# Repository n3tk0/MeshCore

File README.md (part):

> **This is a fork of [meshcore-dev/MeshCore](https://github.com/meshcore-dev/MeshCore).**
> It tracks upstream and adds a Faketec v5 companion build with its own encoder-driven UI (read and write messages without a phone), a mailbox and LoRa OTA updates for repeaters (with an Android app and an nRF52 bootloader that survives power cuts), light builds of any board, plus robustness fixes to the shared MeshCore code.
> Everything below "About MeshCore" is the upstream README. For general MeshCore support, issues and contributions, please use the upstream repository.

## 🍴 What this fork adds

- [Faketec v5 companion with encoder UI](#faketec-v5-companion-with-encoder-ui): hardware, wiring, controls, writing messages, settings, build flags
- [Repeater mailbox](#repeater-mailbox-store--forward-for-direct-messages): keeps direct messages for owners who are away
- [LoRa OTA for repeaters](#lora-ota-for-repeaters-nrf52-esp32): delta updates over the air from an Android app
- [Repeater battery from an INA219](#repeater-battery-from-an-ina219) and [repeaters that look after themselves](#repeaters-that-look-after-themselves): charge counting, battery saving steps (`battsave`), self test, telemetry history
- [nRF52 bootloader for LoRa OTA](#nrf52-bootloader-for-lora-ota): staged install that survives a power cut, rollback on boards with QSPI flash
- [Fixes to upstream MeshCore](#fixes-to-upstream-meshcore): crash and hang fixes that apply to every board
- [New shared components](#new-shared-components): reusable drivers and hooks added under `src/` and `examples/companion_radio/`
- [Builds and CI](#builds-and-ci)

> Status: the Faketec v5 firmware compiles and boots with BLE. The UI has been checked in the screen simulator (`tools/ui-sim`); the latest changes (network tools, channels from the device, learned words, hardware check, buttons instead of the encoder, repeat) have not been tested on hardware yet. The repeater mailbox, LoRa OTA and the bootloader pass their unit and host tests and build in CI, but have not been tested on hardware yet either; neither have the battery steps, self test, telemetry history and the app's Health and "Update several" pages.

### Faketec v5 companion with encoder UI

A companion radio build for a Faketec v5 (rev A) board without the on-board BMS/MOSFET, with a local screen and jog-dial controls so the node can be used without a phone. User manual in Bulgarian: [docs/faketec-companion.bg.md](./docs/faketec-companion.bg.md).

| Part | Used here |
|---|---|
| MCU | Nice!Nano v2 / nRF52840 Pro Micro clone |
| Radio | Heltec HT-RA62 (SX1262) |
| Display | 128x64 SSD1306 I2C OLED (e.g. WINSTAR WEA012864) |
| Encoder | Quadrature rotary encoder with push switch (e.g. ZIPPY AN-P1S-2SP-Z), or three buttons instead (see below) |
| Buttons | User button (Back) and reset; use 2-pin switches, a 4-pin switch shorts on the SW1/SW2 footprint |
| Haptics | 3 V coin vibration motor on the board's T2 MOSFET footprint (optional) |
| Power | 1S LiPo straight from the controller's charger, battery read through a divider |

**Wiring**

| Function | Pin |
|---|---|
| Encoder A / B | P1.01 / P1.02 (common to GND) |
| Encoder push | P1.07 |
| Buttons instead of the encoder | Up P1.01, Down P1.02, Enter P1.07 (each to GND) |
| User button (Back) | P1.00 |
| OLED SDA / SCL | P1.04 / P0.11 (board I2C) |
| Vibration motor | T2 gate = P0.08, motor between B+ and drain pad J7, flyback diode across the motor |

**Controls** (Sony Ericsson CMD-Z7 style jog dial, UI in [`examples/companion_radio/ui-encoder`](./examples/companion_radio/ui-encoder))

| Input | Action |
|---|---|
| Turn | Move in lists, scroll a conversation; on standby, next status card (summary, recently heard, radio, battery, GPS) |
| Press | Open / confirm; in a conversation, reply to the selected message |
| Hold press | Quick menu (advert nearby, advert to the whole mesh, transmit on/off, Bluetooth, GPS, power off) or the actions of the current item |
| Back (BTN) | Back one level; on standby, screen off |
| Hold Back | Standby from anywhere; on standby, lock the keys (hold Back again to unlock); while the boot splash shows, CLI rescue |
| Hold Back + press 2.5 s | Power off ("Power off" shows, a double buzz confirms; does nothing while the keys are locked). To switch on, hold Back + press together ~1.5 s until it buzzes; a shorter press goes back to sleep. With USB power it starts at once. In quiet mode neither buzzes |

**Messages**

- **Messages** lists conversations (contacts and channels), newest first, with the unread count or the age of the last message. A conversation opens as a chat: every message wrapped over as many rows as it needs, my messages with their delivery icon, the age of the selected one in the title. Press replies, hold opens Reply / Resend / Delete.
- **Channels** opens a channel's conversation (or the reply picker when it has none yet). Hold on a channel: write, mute (no buzz or screen wake, except for mentions; stored in `/ui_mute`) or delete. The last row, **+ Add**, joins a `#hashtag` channel typed on the keyboard (key = first 16 bytes of `sha256("#name")`, the same as the app).
- **Message details:** hold on a message > Details shows the time, the route (direct / flood / hops), SNR and RSSI of a received message, or the attempts and state of a sent one.
- **Reply** first asks **Quick reply** or **Write**. A quick reply can be sent as is or finished on the keyboard. Replies go to where the message came from (contact or channel).
- **Sending** waits 3 s with a progress bar; Back cancels it. Direct messages are tracked: a clock until the ACK, then a check mark. Without an ACK the message is sent again automatically with the same timestamp (the recipient shows it once), the last attempt as a flood; after 3 attempts it is marked not delivered with a long vibration, and **Resend** starts a new round. Channel messages have no ACK and show as sent.
- **Mentions:** a channel message with `@name` or `@[name]` for this node vibrates and wakes the screen like a direct message.
- **Recipient list:** channels (`#`) first, then chat and room contacts, sorted by name or by last heard. Sorted by name, a row of first letters sits on top: turn left from the first entry, press, turn to a letter, press to jump to the first name with it.
- **Keyboard:** BG, EN and 123 layouts with shift (automatic capital at the start and after `. ! ?`), space, language and send keys. Turn to pick a key, press to type, Back deletes, hold opens Send / Clear / Discard. An unsent message is kept for its recipient while you write elsewhere.
- **Next word:** after a space, the word you most often sent after the previous one is suggested (pairs learned from sent messages, up to 192, ~3.5 KB in `/ui_pairs`; punctuation breaks the chain; Settings > Messages > Learned words > Clear also clears them).
- **Word prediction:** the most frequent dictionary word for what you are typing is shown after the cursor and is selected right after each letter: **press** accepts it and adds a space, turning goes back to the keys. The dictionary (6000 Bulgarian + 4000 English words, ~71 KB flash) is chosen by the script you type in; words you typed recently are suggested first. It is generated by [`ui-encoder/tools/gen_dict.py`](./examples/companion_radio/ui-encoder/tools/gen_dict.py) from [FrequencyWords](https://github.com/hermitdave/FrequencyWords) (CC-BY-SA-4.0). Learned words: words you send that the dictionary lacks (names, places, slang; 3+ letters) are learned, up to 128, stored in `/ui_words`, and suggested before dictionary words.
- **Nothing is lost before the app syncs:** every message for the phone app is written to flash as it arrives (`-D OFFLINE_QUEUE_PERSIST`, an append-only log) and leaves it only when the app has fetched it, so it survives a reset, a hang or a flat battery (up to 256 messages; when full, the oldest channel messages go first). The device's own history (last 24) is not cleared by a sync; it is written within 10 minutes of a change, at power off and before an update. Messages sent from the device do not appear in the phone app's history.

- **Quiet hours:** Settings > Messages > Quiet hours (off, 22–07, 23–07, 00–07, 22–06, 23–06): in those hours channel messages neither wake the screen nor vibrate; direct messages and mentions still do. Only with a valid clock (from the app or an advert); without one it is off.
- **"I'm back":** after a power-on or a wake from sleep/hibernate, and when a repeater is heard again after 10+ minutes without one (its advert, or any flood packet it passes on, so a node that stays near a repeater does not do it every hour), the companion sends one zero-hop advert by itself (at most once in 10 minutes, only while transmit is on), so a repeater's mailbox hands over at once (`-D BACK_ADVERT`). When the mailbox delivers, the screen shows "Mailbox: N msgs".
- **Battery:** the battery card shows the voltage and the time left (e.g. `3.8V ~18h`), from how fast the percentage fell over the last hours; the next card is a 24-hour graph of the battery with its low–high %. The history (every 10 minutes for 24 h, every hour for a week, `-D TELEMETRY_HISTORY`) is kept in `/tele_hist` and the app reads it (BLE command 121).

**Network** (Menu > Network)

- **Nearby:** a zero-hop discover request; the repeaters that answer in 10 s, strongest first. A repeater shows how well it hears us (↑) and we hear it (↓), and starts a trace or range test to it. Hold searches again.
- **Trace:** from a contact (hold > Trace) or a nearby repeater: a TRACE packet there and back through the repeaters of its path, with the SNR at each hop and the round-trip time.
- **Airtime:** transmit time in the last hour against the EU 868 MHz 10% duty cycle, total TX time, packets sent / received / errors, noise floor, last SNR and RSSI.
- **Range test:** a trace to the chosen repeater or contact every 15 / 30 / 60 / 120 s, a buzz for each answer (a different one for a miss), the last results with SNR there and back. Keeps running with the screen off until stopped (an icon in the standby status row shows it); stops if transmit is switched off.

**Settings** (Menu > Settings, saved in prefs)

| Group | Settings |
|---|---|
| Display | menu font and text font size (large / medium / small / tiny), screen timeout (15 s – 5 min), brightness, page dots |
| Hardware | encoder direction, encoder steps per detent (2 / 4; hidden with buttons), vibration, keyboard jump to the likely next letter, key lock (by hand / automatic when the screen goes off), input test, vibration test, screen test, readings (battery raw/ADC, USB, reset reason, noise floor, uptime) |
| Messages | alerts (without phone / always / never), wake the screen for (direct and mentions / all / never), quiet hours, confirm deletes, contacts sort, 10 quick replies (stored in `/ui_quick`), learned words (count, clear) |
| Radio | transmit on/off, TX power, antenna question (after a new battery / every boot / never), preset (EU/UK Narrow, EU/UK Deprecated; anything else shows as custom), repeater |
| System | node name (an advert with the new name is offered; the Bluetooth name changes after a restart), language BG / EN, time zone, EU summer time, battery calibration, about, CLI rescue, firmware update over USB (UF2 drive) or BLE (DFU) |

**Buttons instead of the encoder:** Up on P1.01, Down on P1.02 and Enter on P1.07, each to GND. The firmware is the same: after a new battery, the first turn or press at the antenna question shows which is fitted, and that is remembered across restarts and power off. A held button repeats. A wrong guess fixes itself: two full encoder clicks in one direction within 1 s switch to the encoder, two presses of one button within 2 s switch to buttons.

**Repeater (emergency only):** Settings > Radio > Repeater (or the phone app) makes the companion repeat other nodes' packets. It loads the mesh and the battery, so it asks "Emergency only! Turn on?" first, and a tower icon shows in the status row while it is on. It is allowed on 433.000, 869.495, 869.618 (EU/UK Narrow) and 918.000 MHz (`-D ALLOWED_REPEAT_FREQ_RANGE` in the Faketec ini); while it is on, a preset on another frequency is refused.

**Battery calibration:** Settings > System > Battery shows the measured voltage; set it to what a multimeter shows at the battery and the divider factor is saved in prefs. The shown value is averaged, and the node powers off only after three low readings in a row, so a transmit pulse does not switch it off.

**Watchdog:** the nRF52 hardware watchdog (30 s, `-D WATCHDOG_SECONDS`) restarts a node whose main loop hangs, e.g. on a stuck I2C bus, so the low-battery cutoff keeps working. The bootloader feeds it, so DFU and UF2 updates are not affected.

**Build flags** (in [`variants/faketec_v5/platformio.ini`](./variants/faketec_v5/platformio.ini))

- `-D DISPLAY_CYRILLIC`: Cyrillic 5x8 font for the SSD1306.
- `-D PIN_VIBRATION`, `-D VIBRATION_PWM=190`: haptic patterns (key click, confirm, channel / direct message, power off); PWM keeps the motor near 3.1 V on a full LiPo. Remove to build without a motor.
- `-D AUTO_SHUTDOWN_MILLIVOLTS=3300`: there is no BMS, so the node hibernates below this voltage. Calibrate in Settings > System > Battery (or set `-D ADC_MULTIPLIER` for your divider).
- `-D ENCODER_STEPS_PER_DETENT=2`, `-D ENCODER_REVERSE=true`: build defaults for the encoder; both can also be changed in Settings.
- `-D DISABLE_RTC_AUTODISCOVERY`, `-D DISABLE_ENV_SENSORS`: skip the RTC probes and the sensor scan when none are fitted (a faster boot; a bad I2C bus no longer hangs it, see below).
- `-D ALLOWED_REPEAT_FREQ_RANGE=...`: the frequencies where the repeater setting may be turned on (upstream allows 433.000, 869.495 and 918.000 MHz; this build adds 869.618).

Build with PlatformIO, e.g. `pio run -e Faketec_v5_companion_radio_ble` (or `_usb`), then flash the UF2 by double-tapping reset and copying it to the bootloader drive.

### Repeater mailbox (store & forward for direct messages)

Every repeater built from this fork (`-D NO_MAILBOX` leaves it out) can keep direct messages for up to 4 owner companions while they are away, and hand them over when the owner is heard again with no hop between. Nothing is flooded: messages are kept from traffic the repeater hears anyway, and handed over as zero-hop packets that nobody repeats.

- **What is kept:** only `TXT_MSG` packets addressed to an owner (by the first public key byte, the only one in the packet), still encrypted to the owner; the repeater cannot read them. Channel messages, adverts and messages sent with no hop (the owner is next to the sender, or another mailbox is handing over) are not kept. Off until `mailbox learn` or `mailbox on`. Up to 64 messages (8 on STM32) in flash (`/mailbox`), so they survive a restart; older than `ttl` hours are dropped (after a restart without a clock, the age counts from the restart); when full, the oldest goes.
- **Only while away:** an owner heard with no hop in the last `away` minutes (its signed advert, or its ACK to a message this mailbox handed over; a packet that only carries the first key byte does not count, since a neighbour may share it) is present, and nothing is kept for it. A flood message the owner answered with a PATH reply in the next 2 minutes is dropped as delivered. A sender's automatic retries (same sender, same length, within 30 s) are kept once.
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
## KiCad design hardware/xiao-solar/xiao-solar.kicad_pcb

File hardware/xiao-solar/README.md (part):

# Xiao solar board

Платка в стил Faketec за **Seeed XIAO nRF52840 + Wio-SX1262 for XIAO** с MPPT соларно
зареждане, power path, защита на батерията, температурен сензор, контролер MSPM0L1306 (зарядно,
ток на батерията, подгряване на батерията) и I2C гребен за външна периферия.
Всичко освен Xiao, Wio и конекторите се сглобява от JLCPCB (всички части са на склад в JLC
към 2026-10-29).

Статус: **v0.5: схема + разводка** (50×65 mm, 2 слоя, SMD части само отгоре). Не е поръчвана/тествана.

v0.5 (2026-11-11, решения в `/mnt/project-files/notes/xiao-solar-v05-2026-11-11.md`, всички ★):
- **MSPM0L1306** (U6) вместо INA219, със същите изводи като на `solar-smart-mppt`, така че фърмуерът
  му (PR #36) върви с отделен board header. Управлява BQ25798 по собствена I2C шина (I2C1,
  SCL_I/SDA_I, pull-up R14/R15 към 3V3M), а за Xiao се вижда като **INA260 на 0x41** + наша карта
  на **0x42** (I2C0 на шината на Xiao, на изводите PA0/PA1: open-drain, без диод към 3V3M, pinmux-ът
  е различен от solar-smart-mppt). Xiao вече не пипа BQ25798.
- **3V3M**: собствен HT7533 (U8, 2.5 µA) от SYS, само за MSPM0 и неговите pull-up/делители:
  MSPM0 пази батерията и нагревателя, докато Xiao се флашва, рестартира или виси.
- **Шунт 50 mΩ = RS1 ∥ RS2** (2× 100 mΩ 1%, 1206, 250 mW, C25334 basic, без такса; 2026-11-12, т. 1а
  в `notes/xiao-solar-v05-cost2-2026-11-12.md`) в минуса: HJ8205 (S2, BATT_S) → RS1/RS2 → GND.
  Двата са вертикално един под друг на 1.5 mm от десния ръб (V-cut), с дългата страна успоредно
  на ръба (2026-11-13: преди бяха хоризонтални на 0.47 mm от V-cut). BATT_S е на двата вътрешни
  пада, GND на външните. При 2 A всеки поема 1 A и губи 0.1 W. Kelvin на RS2: R21 отива отделно до
  BATT_S пада му, R22 взима SH_K от net tie NT1 на GND пада му (всичко по F.Cu), C24 между входовете, R23/R24 330k (C25778) към 3V3M ги вдигат с ~97 mV (OPA0/OPA1 на
  PA25/PA18), така че разрядът се мери до ~1.9 A (с 1M беше ~33 mV, т.е. само 0.66 A при 50 mΩ;
  цената е ~13 µA повече от 3V3M). + = заряд. Сигналът е 2.5× по-голям от стария 20 mΩ; токът се дели между двата
  резистора и медта добавя ~1–2 %, затова фърмуерът калибрира наклона веднъж при известен ток.
  Температурният коефициент е ~800 ppm/°C (~±3 % от −20 до +60 °C).
- **DW01A + HJ8205 остават** като независима хардуерна защита; CS (R10) е на страната на FET-овете
  (BATT_S), прагът за късо не се променя.
- **~CE** е на MSPM0 (PA17) с R4 100k към 3V3M: без MSPM0 няма заряд (LiFePO4 е безопасно).
  **JP2 = CHEM** към PA23 (отгоре над MSPM0, надпис LFP): отворен = Li-ion, затворен = LiFePO4. За LiFePO4 се затварят JP2 и JP3. D0 на Xiao е свободен.
- **VBAT** за ADC на MSPM0: R25 1M / R26 470k + C30 (PA24/A3).
- **Нагревател** J6 (HEAT, 2 пина): + = SYS, − = дрейн на Q4 (AO3400A), гейт R27 100R от PA26,
  R28 100k към GND (без MSPM0 / при рестарт е изключен). Червен LED D6 + R29 1k успоредно на
  нагревателя (до J6) свети, докато Q4 е включен (при малък PWM по-слабо), ~2 mA. Подробно в блок 8.
- **SWD** на MSPM0: пет пада отдолу в един ред на 2.54 mm под реда изводи на Wio. Гледано отдолу,
  отдясно наляво са 3V3M, NRST, SWDIO, SWCLK и GND, с надписи.
- **Подредба** (Петко, 2026-11-11): платката е 50×75 mm. SOLAR (J1), BAT (J4) и NTC (J3) са на
  долния ръб, HEAT (J6) е на десния ръб над долния отвор, на една линия с I2C гребена J5 (единственият
  конектор горе). BMS (DW01A, HJ8205, шунт) е долу вдясно. U6 (MSPM0) и U8 (HT7533) са преместени
  нагоре и вдясно, далеч от U3 (по-лесно запояване). **Вторият вход VIN2 (J2, D2) е махнат**; D1 SS54
  остава като защита от обратна полярност на панела.
- **Цена и размер** (Петко, 2026-11-12, `notes/xiao-solar-v05-ideas-2026-11-12.md`):
  - **Без SHT40** (и без езика с прорезите). MSPM0 отговаря на I2C на Xiao и като **MLX90614 на 0x5A**
    (стандартен сензор в MeshCore): "обект" = батерията (NTC през TS_ADC на BQ25798, one-shot ADC),
    "околна" = вътрешният сензор на MSPM0 (температура на платката). Влажност вече няма.
  - **D5 (LM66100) е заменен с дискретен идеален диод**, както на solar-smart-mppt: Q5 AO3401A
    (D към SYS, S към 5V на Xiao), огледало Q6/Q7 MMBT3906 (preferred, без такса) и R30/R31 1M.
    Q7 затваря Q5, щом 5V на Xiao (USB) е над SYS, така че ток не тече обратно в SYS.
  - **C9** (100 nF на PMID) е 0603 basic вместо 0402 extended; стои изправен точно над пин 29.
  - **50×65 mm** (Петко, 2026-11-12, след DFM отчета на JLC; преди това 50×60 по негова скица): Xiao (U3, вляво) и Wio (U4, вдясно, обърнат
    на 180°) са един до друг под горния ръб. Идеалният диод (Q5–Q7, R30/R31) е в процепа между
    тях. Под модулите има лента: C20, HT7533 (U8) с C25/C26, C21, MSPM0 (U6), VBAT делителят, JP2
    (LFP) и BMS-ът вдясно. Отдолу под Wio е редът SWD. Зарядното е вдигнато с 10 mm, а конекторите
    са по долния ръб. J5 (I2C) е горе вляво над Xiao (отляво надясно SCL, SDA, 3V3, GND). Има **4 отвора**.
  - Шунтът (RS2 над RS1, вертикално до десния ръб): BATT_S идва от Q3 по F.Cu (0.8 mm) под колоната
    R21/C24/R22 и влиза между двата вътрешни пада. Външните GND падове са плътно към площта, с via
    над RS2 и под RS1. R10 (CS на DW01A) стига до BATT_S по B.Cu. Захранването на нагревателя
    (SYS, 1.2 mm) минава вляво от RS1 и под него до J6.
    Линиите Xiao↔Wio се развеждат предварително около модулите (`PRE_ROUTES`): SPI и 3V3 по B.Cu
    над изводите на Xiao, надолу през процепа и в долните изводи на Wio отдолу; LoRa управлението
    (DIO1, RST, BUSY, NSS, RXEN) под Xiao, после по F.Cu над Wio. **Под Wio няма писти на нито един
    слой** (`WIO_IN`: keepout за Freerouting и за предварителната разводка), там и двата слоя са GND.
  - 50×65 спрямо 50×60: всеки SMD пад е на ≥ 3 mm от изводите на модулите и конекторите (THT↔SMD
    по DFM на JLC; SWD падовете бяха на 1.5 mm, C28 на 0.96 mm). Координатите в `gen_pcb.py` са
    тези на 50×60, а `ys()` ги разтяга: +1 mm под горния ред, +3.1 mm от лентата под модулите
    надолу и +5 mm за долния ред конектори. Q4 и частите на нагревателя са 1.5 mm по-наляво от J6.
    R28 е 0603 (100k, basic).
  - GND на B.Cu е на 4 парчета (линиите SPI и I2C към J5 я пресичат), всяко свързано с F.Cu с
    поне 2 via, а големите с 20+.
  - (Преди това 50×70 с 3 отвора, commit ad6be5a.)
  - След Freerouting има няколко ръчни поправки направо в `.kicad_pcb`, които генераторът не прави:
    захранването на HT7533 (SYS) по B.Cu покрай C28, GND мост C30↔R26, via за R31 и процепа,
    DW_VCC към C19, OR_G от R31, SWDIO и REGN краища, а от 2026-11-12 и RS2 с връзките около
    шунта (от 2026-11-13 генераторът ги поставя и развежда сам).
    Повторно пускане на тръбата ги губи.
  - Extended части с такса: 4 (BQ25798, MSPM0, L1, DW01A); шунтът вече е basic.
- **CPL: Q3 (HJ8205) е с ротация +270°** (2026-11-13). Платката ползва за него footprint-а на DW01A
  (изводи в два реда), а моделът на JLC за C20069150 е с изводи в две колони. Без корекцията JLC
  щеше да го сложи завъртян на 90°. Поправено и в CPL на xiao-solar-lite. Останалите части са
  сверени пад по пад с footprint-ите на JLC (`ROT_FIX` / `ROT_LCSC` в `tools/export.py`).
- NTC на J3 остава на TS на BQ25798; MSPM0 го чете през TS_ADC на BQ (без нови части), JEITA на BQ остава.
- Разводка: BATT+ (до 3 A) минава от Q2/JP3 по F.Cu (1.0 mm, 0.8 mm на последните 7 mm) до J4, BATT− по B.Cu (1.0 mm) с два
  via до Q3; захранването на
  нагревателя е 1.2 mm по F.Cu от SYS медта до J6, връщането 1.0 mm от Q4.
- Разводка по опита от `solar-smart-mppt`: изводите на MSPM0 са изведени на ръка (заключени писти
  0.2 mm до via), аналоговите линии (шунт, VBAT, CHEM, нагревател) и I2C1 към BQ25798 са разведени
  преди Freerouting (`tools/patch2.py`), шината SCL_I/SDA_I/~CE слиза по B.Cu до зарядното.
  Последните GND острови се връзват с `tools/gndfix.py`. DRC: 0 несвързани, 0 грешки по мед.
- Броят extended части с такса не се променя (MSPM0 и шунтът заместват INA219 и стария шунт).

v0.3 (преглед 2026-10-29): зарядната зона е преработена по layout guide на BQ25798
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
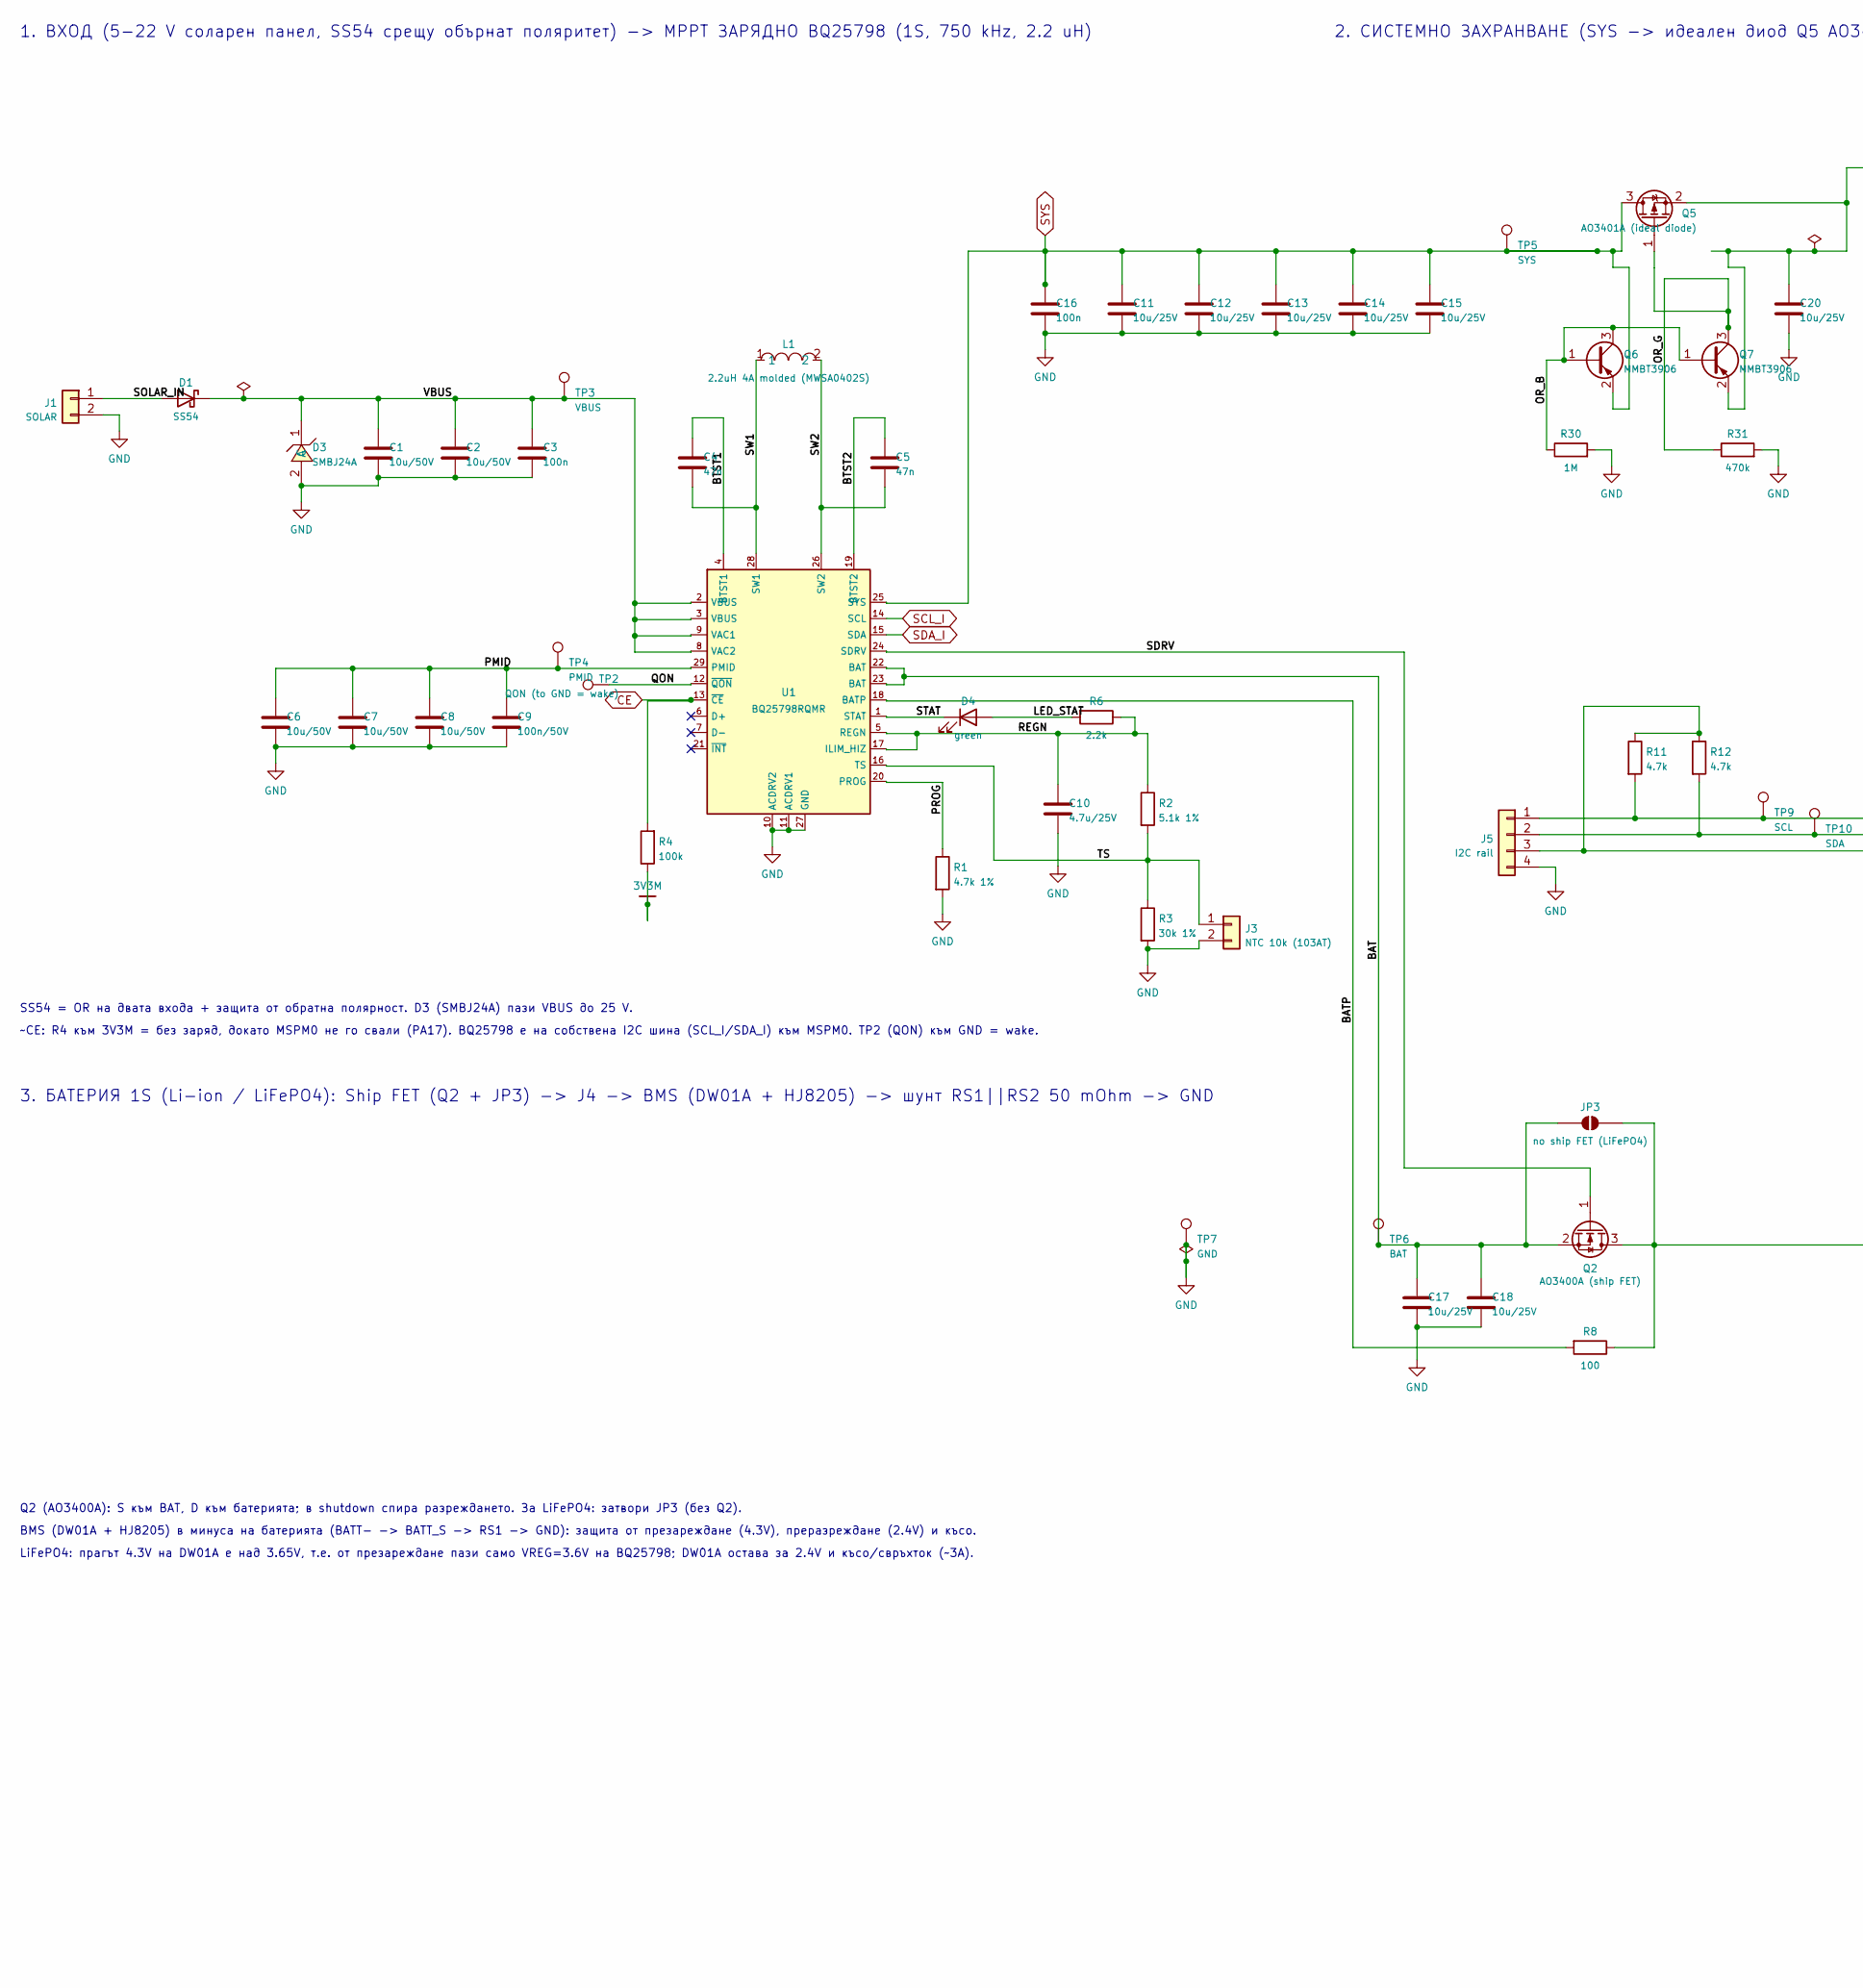
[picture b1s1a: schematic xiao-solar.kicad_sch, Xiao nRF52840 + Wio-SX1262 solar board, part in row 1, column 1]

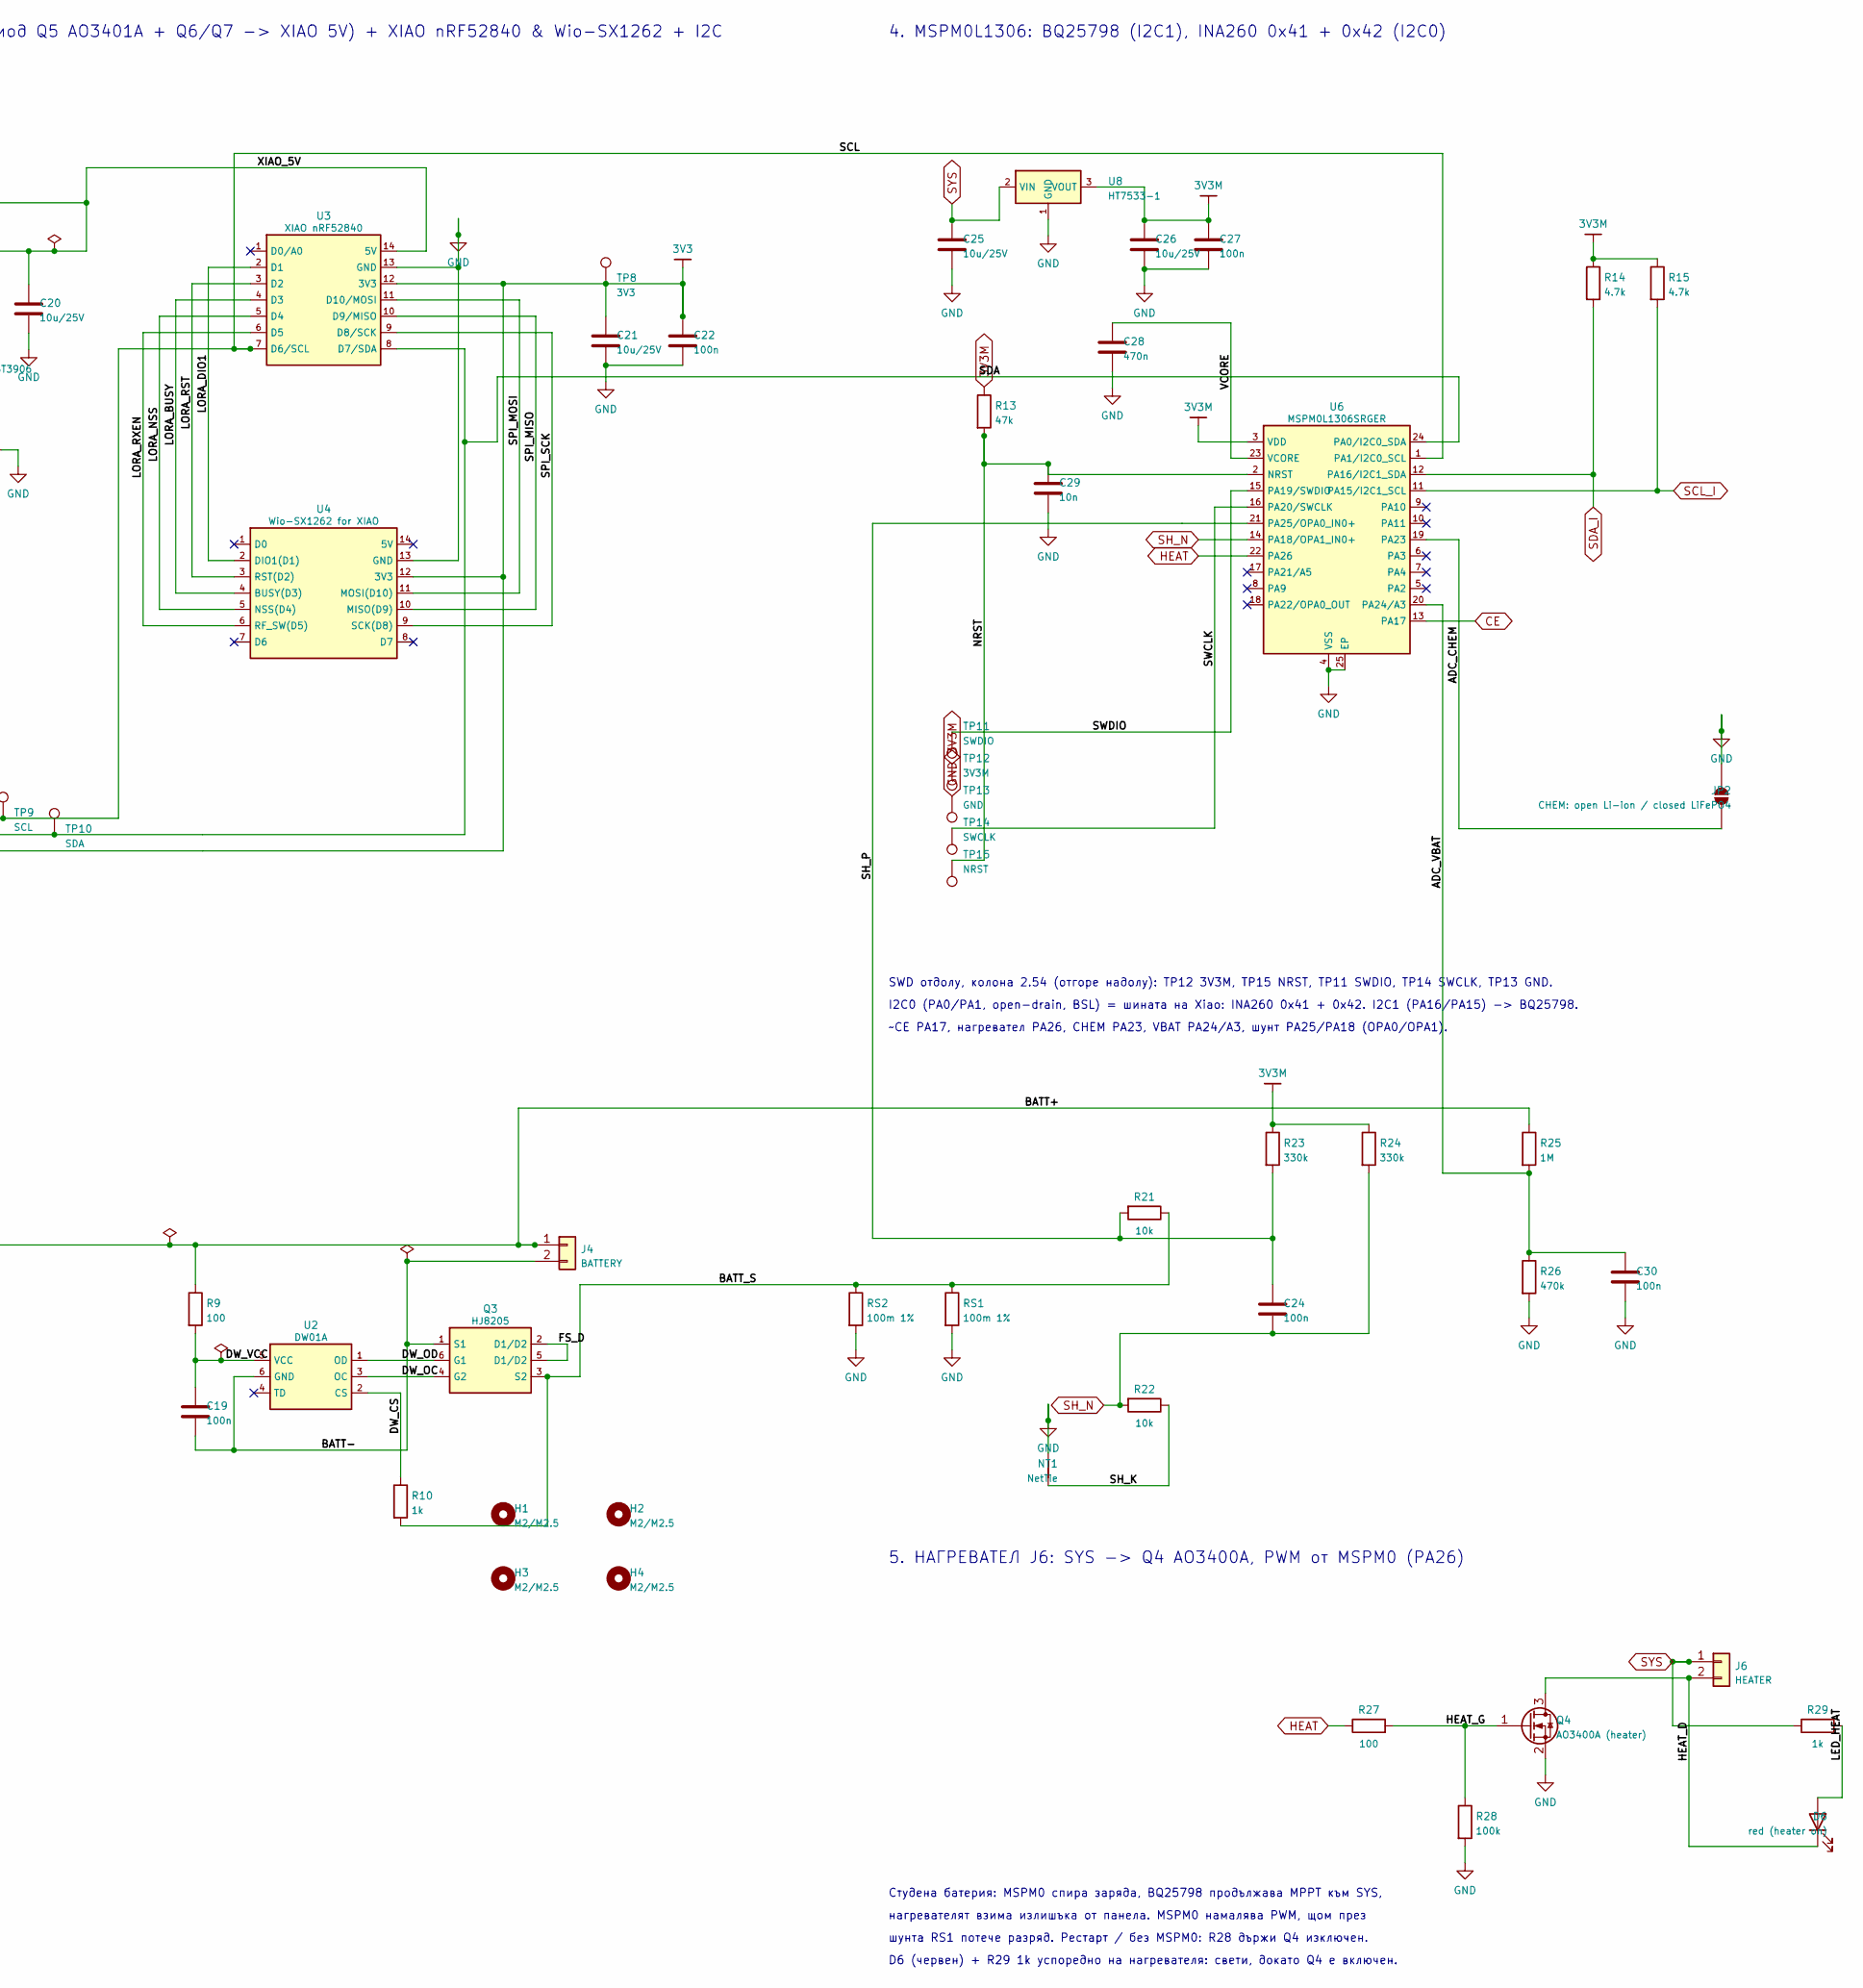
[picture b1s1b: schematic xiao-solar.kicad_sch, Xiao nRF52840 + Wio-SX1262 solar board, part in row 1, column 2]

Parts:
C1, C2, C6, C7, C8: 10u/50V; C_1206_3216Metric; LCSC C13585
C3, C19, C22: 100n; C_0603_1608Metric; LCSC C14663
C4, C5: 47n; C_0603_1608Metric; LCSC C1622
C9: 100n/50V; C_0603_1608Metric; LCSC C14663
C10: 4.7u/25V; C_0805_2012Metric; LCSC C1779
C11, C12, C13, C14, C15, C17, C18, C20, C21, C25, C26: 10u/25V; C_0805_2012Metric; LCSC C15850
C16, C24, C27, C30: 100n; C_0402_1005Metric; LCSC C1525
C28: 470n; C_0603_1608Metric; LCSC C1623
C29: 10n; C_0402_1005Metric; LCSC C15195
D1: SS54; D_SMA; LCSC C22452
D3: SMBJ24A; SMB_L4.6-W3.6-LS5.3-RD; LCSC C19077578
D4: green; LED_0805_2012Metric; LCSC C2297
D6: red (heater on); LED_0805_2012Metric; LCSC C84256
H1, H2, H3, H4: M2/M2.5; MountingHole_2.8mm_Keepout6mm
J1: SOLAR; PinHeader_1x02_P2.54mm_Vertical
J3: NTC 10k (103AT); PinHeader_1x02_P2.54mm_Vertical
J4: BATTERY; PinHeader_1x02_P2.54mm_Vertical
J5: I2C rail; PinHeader_1x04_P2.54mm_Vertical
J6: HEATER; PinHeader_1x02_P2.54mm_Vertical
JP2: CHEM: open Li-ion / closed LiFePO4; SolderJumper-2_P1.3mm_Open_RoundedPad1.0x1.5mm
JP3: no ship FET (LiFePO4); SolderJumper-2_P1.3mm_Open_RoundedPad1.0x1.5mm
L1: 2.2uH 4A molded (MWSA0402S); IND-SMD_L4.4-W4.2_MWSA0402S; LCSC C408335
NT1: NetTie; NetTie-2_SMD_Pad0.5mm
Q2: AO3400A (ship FET); SOT-23; LCSC C20917
Q3: HJ8205; SOT-23-6_L2.9-W1.6-P0.95-LS2.8-BL; LCSC C20069150
Q4: AO3400A (heater); SOT-23; LCSC C20917
Q5: AO3401A (ideal diode); SOT-23; LCSC C15127
Q6, Q7: MMBT3906; SOT-23; LCSC C7420354
R1: 4.7k 1%; R_0603_1608Metric; LCSC C23162
R2: 5.1k 1%; R_0603_1608Metric; LCSC C23186
R3: 30k 1%; R_0603_1608Metric; LCSC C22984
R4, R28: 100k; R_0603_1608Metric; LCSC C25803
R6: 2.2k; R_0603_1608Metric; LCSC C4190
R8, R9, R27: 100; R_0603_1608Metric; LCSC C22775
R10, R29: 1k; R_0603_1608Metric; LCSC C21190
R11, R12: 4.7k; R_0603_1608Metric; LCSC C23162
R13: 47k; R_0402_1005Metric; LCSC C25792
R14, R15: 4.7k; R_0402_1005Metric; LCSC C25900
R21, R22: 10k; R_0402_1005Metric; LCSC C25744
R23, R24: 330k; R_0402_1005Metric; LCSC C25778
R25: 1M; R_0402_1005Metric; LCSC C26083
R26, R31: 470k; R_0603_1608Metric; LCSC C23178
R30: 1M; R_0603_1608Metric; LCSC C22935
RS1, RS2: 100m 1%; R_1206_3216Metric; LCSC C25334
TP2: QON (to GND = wake); TestPoint_Pad_D1.0mm
TP3: VBUS; TestPoint_Pad_D1.0mm
TP4: PMID; TestPoint_Pad_D1.0mm
TP5: SYS; TestPoint_Pad_D1.0mm
TP6: BAT; TestPoint_Pad_D1.0mm
TP7, TP13: GND; TestPoint_Pad_D1.0mm
TP8: 3V3; TestPoint_Pad_D1.0mm
TP9: SCL; TestPoint_Pad_D1.0mm
TP10: SDA; TestPoint_Pad_D1.0mm
TP11: SWDIO; TestPoint_Pad_D1.0mm
TP12: 3V3M; TestPoint_Pad_D1.0mm
TP14: SWCLK; TestPoint_Pad_D1.0mm
TP15: NRST; TestPoint_Pad_D1.0mm
U1: BQ25798RQMR; QFN-29_L4.0-W4.0-P0.40-TL-BQ25792RQMR; LCSC C2876593
U2: DW01A; SOT-23-6_L2.9-W1.6-P0.95-LS2.8-BL; LCSC C351410
U3: XIAO nRF52840; XIAO_14P_2.54_21x17.8mm
U4: Wio-SX1262 for XIAO; XIAO_14P_2.54_21x17.8mm
U6: MSPM0L1306SRGER; VQFN-24-1EP_4x4mm_P0.5mm_EP2.45x2.45mm; LCSC C19189323
U8: HT7533-1; SOT-89-3_L4.5-W2.5-P1.50-LS4.2-BR; LCSC C14289

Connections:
3V3: C21.1, C22.1, J5.3, R11.1, R12.1, TP8.1, U3.12 (3V3), U4.12 (3V3)
3V3M: C26.1, C27.1, R4.1, R13.1, R14.1, R15.1, R23.1, R24.1, TP12.1, U6.3 (VDD), U8.3 (VOUT)
ADC_CHEM: JP2.1 (A), U6.19 (PA23)
ADC_VBAT: C30.1, R25.2, R26.1, U6.20 (PA24/A3)
BAT: C17.1, C18.1, JP3.1 (A), Q2.2 (S), TP6.1, U1.22 (BAT), U1.23 (BAT)
BATP: R8.2, U1.18 (BATP)
BATT+: J4.1, JP3.2 (B), Q2.3 (D), R8.1, R9.1, R25.1
BATT-: C19.2, J4.2, Q3.1 (S1), U2.6 (GND)
BATT_S: Q3.3 (S2), R10.2, R21.1, RS1.1, RS2.1
BTST1: C4.1, U1.4 (BTST1)
BTST2: C5.1, U1.19 (BTST2)
CE: R4.2, U1.13 (~CE), U6.13 (PA17)
DW_CS: R10.1, U2.2 (CS)
DW_OC: Q3.4 (G2), U2.3 (OC)
DW_OD: Q3.6 (G1), U2.1 (OD)
DW_VCC: C19.1, R9.2, U2.5 (VCC)
FS_D: Q3.2 (D1/D2), Q3.5 (D1/D2)
GND: C1.2, C2.2, C3.2, C6.2, C7.2, C8.2, C9.2, C10.2, C11.2, C12.2, C13.2, C14.2, C15.2, C16.2, C17.2, C18.2, C20.2, C21.2, C22.2, C25.2, C26.2, C27.2, C28.2, C29.2, C30.2, D3.2 (A), J1.2, J3.2, J5.4, JP2.2 (B), NT1.2, Q4.2 (S), R1.2, R3.2, R26.2, R28.2, R30.2, R31.2, RS1.2, RS2.2, TP7.1, TP13.1, U1.10 (ACDRV2), U1.11 (ACDRV1), U1.27 (GND), U3.13 (GND), U4.13 (GND), U6.4 (VSS), U6.25 (EP), U8.1 (GND)
HEAT: R27.1, U6.22 (PA26)
HEAT_D: D6.1 (K), J6.2, Q4.3 (D)
HEAT_G: Q4.1 (G), R27.2, R28.1
LED_HEAT: D6.2 (A), R29.2
LED_STAT: D4.2 (A), R6.2
LORA_BUSY: U3.4 (D3), U4.4 (BUSY(D3))
LORA_DIO1: U3.2 (D1), U4.2 (DIO1(D1))
LORA_NSS: U3.5 (D4), U4.5 (NSS(D4))
LORA_RST: U3.3 (D2), U4.3 (RST(D2))
LORA_RXEN: U3.6 (D5), U4.6 (RF_SW(D5))
NRST: C29.1, R13.2, TP15.1, U6.2 (NRST)
OR_B: Q6.1 (B), Q6.3 (C), Q7.1 (B), R30.1
OR_G: Q5.1 (G), Q7.3 (C), R31.1
PMID: C6.1, C7.1, C8.1, C9.1, TP4.1, U1.29 (PMID)
PROG: R1.1, U1.20 (PROG)
QON: TP2.1, U1.12 (~QON)
REGN: C10.1, R2.1, R6.1, U1.5 (REGN), U1.17 (ILIM_HIZ)
SCL: J5.1, R11.2, TP9.1, U3.7 (D6/SCL), U6.1 (PA1/I2C0_SCL)
SCL_I: R15.2, U1.14 (SCL), U6.11 (PA15/I2C1_SCL)
SDA: J5.2, R12.2, TP10.1, U3.8 (D7/SDA), U6.24 (PA0/I2C0_SDA)
SDA_I: R14.2, U1.15 (SDA), U6.12 (PA16/I2C1_SDA)
SDRV: Q2.1 (G), U1.24 (SDRV)
SH_K: NT1.1, R22.1
SH_N: C24.2, R22.2, R24.2, U6.14 (PA18/OPA1_IN0+)
SH_P: C24.1, R21.2, R23.2, U6.21 (PA25/OPA0_IN0+)
SOLAR_IN: D1.2 (A), J1.1
SPI_MISO: U3.10 (D9/MISO), U4.10 (MISO(D9))
SPI_MOSI: U3.11 (D10/MOSI), U4.11 (MOSI(D10))
SPI_SCK: U3.9 (D8/SCK), U4.9 (SCK(D8))
STAT: D4.1 (K), U1.1 (STAT)
SW1: C4.2, L1.1, U1.28 (SW1)
SW2: C5.2, L1.2, U1.26 (SW2)
SWCLK: TP14.1, U6.16 (PA20/SWCLK)
SWDIO: TP11.1, U6.15 (PA19/SWDIO)
SYS: C11.1, C12.1, C13.1, C14.1, C15.1, C16.1, C25.1, J6.1, Q5.3 (D), Q6.2 (E), R29.1, TP5.1, U1.25 (SYS), U8.2 (VIN)
TS: J3.1, R2.2, R3.1, U1.16 (TS)
VBUS: C1.1, C2.1, C3.1, D1.1 (K), D3.1 (C), TP3.1, U1.2 (VBUS), U1.3 (VBUS), U1.8 (VAC2), U1.9 (VAC1)
VCORE: C28.1, U6.23 (VCORE)
XIAO_5V: C20.1, Q5.2 (S), Q7.2 (E), U3.14 (5V)

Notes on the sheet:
1. ВХОД (5-22 V соларен панел, SS54 срещу обърнат поляритет) -> MPPT ЗАРЯДНО BQ25798 (1S, 750 kHz, 2.2 uH)
SS54 = OR на двата входа + защита от обратна полярност. D3 (SMBJ24A) пази VBUS до 25 V.
~CE: R4 към 3V3M = без заряд, докато MSPM0 не го свали (PA17). BQ25798 е на собствена I2C шина (SCL_I/SDA_I) към MSPM0. TP2 (QON) към GND = wake.
2. СИСТЕМНО ЗАХРАНВАНЕ (SYS -> идеален диод Q5 AO3401A + Q6/Q7 -> XIAO 5V) + XIAO nRF52840 & Wio-SX1262 + I2C
3. БАТЕРИЯ 1S (Li-ion / LiFePO4): Ship FET (Q2 + JP3) -> J4 -> BMS (DW01A + HJ8205) -> шунт RS1||RS2 50 mOhm -> GND
Q2 (AO3400A): S към BAT, D към батерията; в shutdown спира разреждането. За LiFePO4: затвори JP3 (без Q2).
BMS (DW01A + HJ8205) в минуса на батерията (BATT- -> BATT_S -> RS1 -> GND): защита от презареждане (4.3V), преразреждане (2.4V) и късо.
LiFePO4: прагът 4.3V на DW01A е над 3.65V, т.е. от презареждане пази само VREG=3.6V на BQ25798; DW01A остава за 2.4V и късо/свръхток (~3A).
4. MSPM0L1306: BQ25798 (I2C1), INA260 0x41 + 0x42 (I2C0)
SWD отдолу, колона 2.54 (отгоре надолу): TP12 3V3M, TP15 NRST, TP11 SWDIO, TP14 SWCLK, TP13 GND.
I2C0 (PA0/PA1, open-drain, BSL) = шината на Xiao: INA260 0x41 + 0x42. I2C1 (PA16/PA15) -> BQ25798.
~CE PA17, нагревател PA26, CHEM PA23, VBAT PA24/A3, шунт PA25/PA18 (OPA0/OPA1).
5. НАГРЕВАТЕЛ J6: SYS -> Q4 AO3400A, PWM от MSPM0 (PA26)
Студена батерия: MSPM0 спира заряда, BQ25798 продължава MPPT към SYS,
нагревателят взима излишъка от панела. MSPM0 намалява PWM, щом през
шунта RS1 потече разряд. Рестарт / без MSPM0: R28 държи Q4 изключен.
D6 (червен) + R29 1k успоредно на нагревателя: свети, докато Q4 е включен.

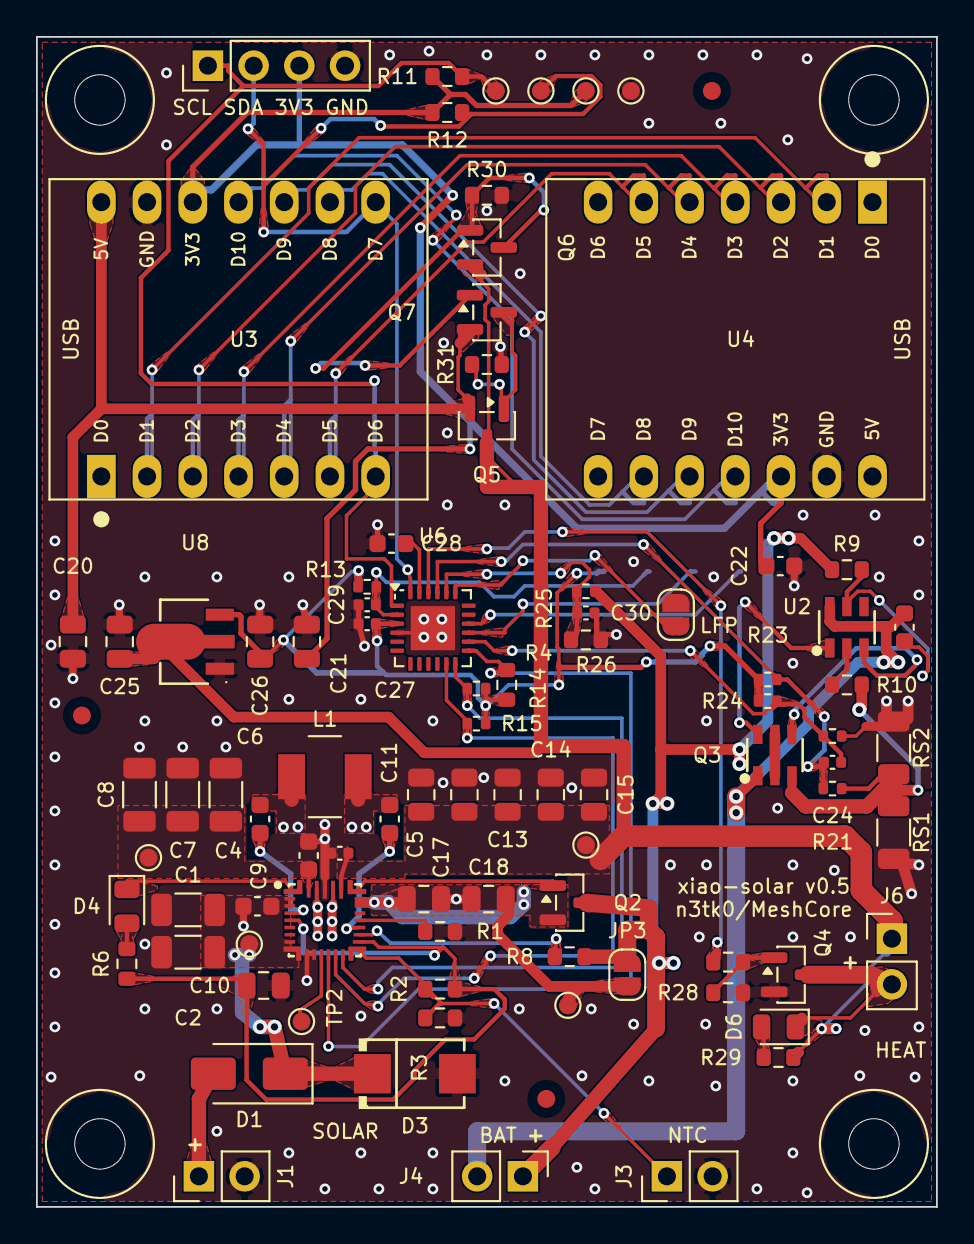
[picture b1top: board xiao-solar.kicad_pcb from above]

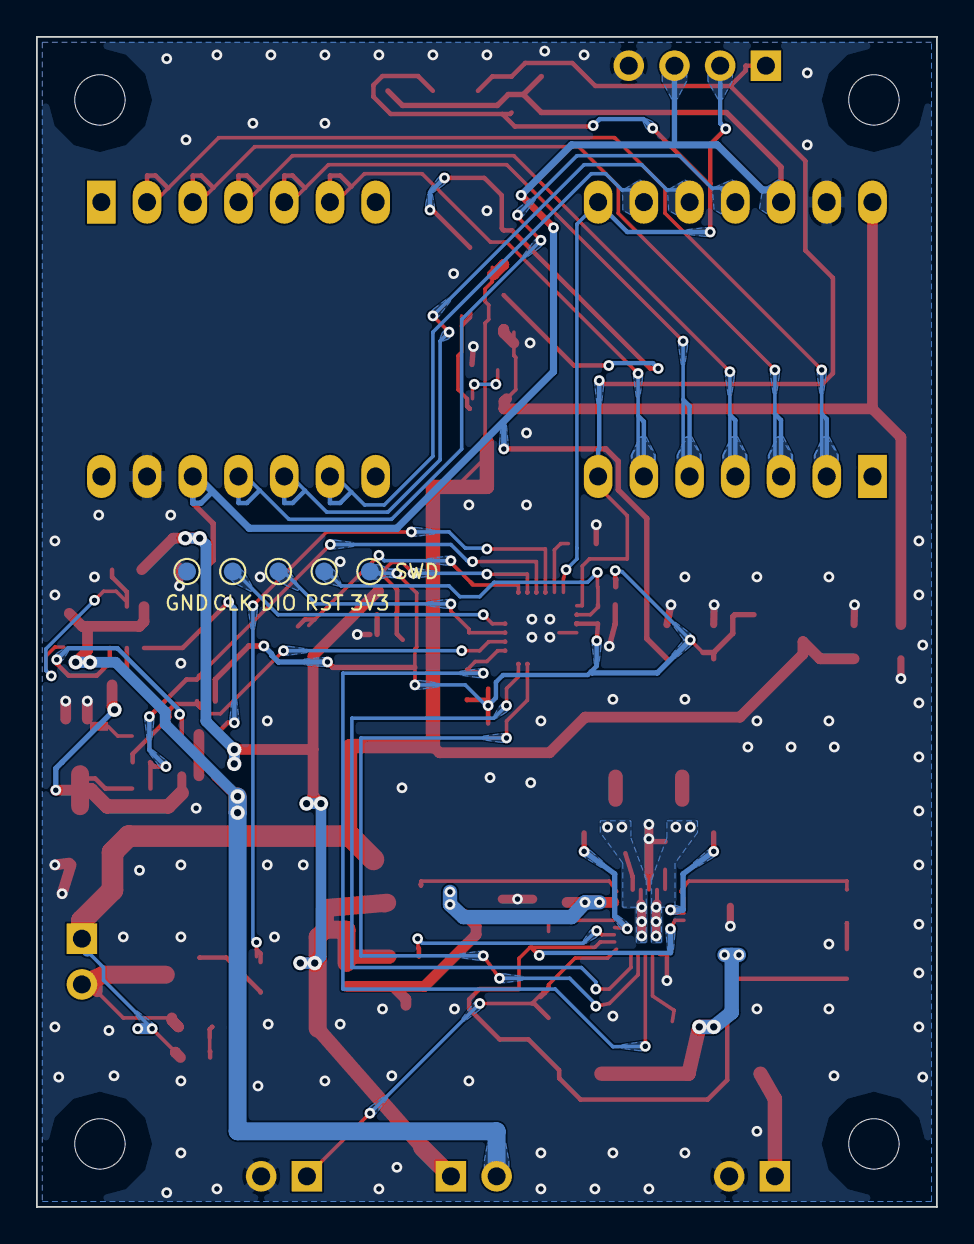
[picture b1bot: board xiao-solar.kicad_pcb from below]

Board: 2 copper layers, 50.0 x 65.0 mm, 101 parts (5 on the bottom side), 57 nets.

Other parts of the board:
FID1, FID2, FID3: Fiducial; Fiducial_1mm_Mask2mm

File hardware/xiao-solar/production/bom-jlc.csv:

Comment,Designator,Footprint,LCSC
10u/50V,"C1,C2,C6,C7,C8",C_1206_3216Metric,C13585
4.7u/25V,C10,C_0805_2012Metric,C1779
10u/25V,"C11,C12,C13,C14,C15,C17,C18,C20,C21,C25,C26",C_0805_2012Metric,C15850
100n,"C16,C24,C27,C30",C_0402_1005Metric,C1525
470n,C28,C_0603_1608Metric,C1623
10n,C29,C_0402_1005Metric,C15195
100n,"C3,C9,C19,C22",C_0603_1608Metric,C14663
47n,"C4,C5",C_0603_1608Metric,C1622
SS54,D1,D_SMA,C22452
SMBJ24A,D3,SMB_L4.6-W3.6-LS5.3-RD,C19077578
green,D4,LED_0805_2012Metric,C2297
red (heater on),D6,LED_0805_2012Metric,C84256
2.2uH 4A molded (MWSA0402S),L1,IND-SMD_L4.4-W4.2_MWSA0402S,C408335
AO3400A (ship FET),"Q2,Q4",SOT-23,C20917
HJ8205,Q3,SOT-23-6_L2.9-W1.6-P0.95-LS2.8-BL,C20069150
AO3401A (ideal diode),Q5,SOT-23,C15127
MMBT3906,"Q6,Q7",SOT-23,C7420354
4.7k 1%,"R1,R11,R12",R_0603_1608Metric,C23162
1k,"R10,R29",R_0603_1608Metric,C21190
47k,R13,R_0402_1005Metric,C25792
4.7k,"R14,R15",R_0402_1005Metric,C25900
5.1k 1%,R2,R_0603_1608Metric,C23186
10k,"R21,R22",R_0402_1005Metric,C25744
330k,"R23,R24",R_0402_1005Metric,C25778
1M,R25,R_0402_1005Metric,C26083
30k 1%,R3,R_0603_1608Metric,C22984
1M,R30,R_0603_1608Metric,C22935
470k,"R26,R31",R_0603_1608Metric,C23178
100k,"R4,R28",R_0603_1608Metric,C25803
2.2k,R6,R_0603_1608Metric,C4190
100,"R8,R9,R27",R_0603_1608Metric,C22775
100m 1%,"RS1,RS2",R_1206_3216Metric,C25334
BQ25798RQMR,U1,QFN-29_L4.0-W4.0-P0.40-TL-BQ25792RQMR,C2876593
DW01A,U2,SOT-23-6_L2.9-W1.6-P0.95-LS2.8-BL,C351410
MSPM0L1306SRGER,U6,VQFN-24-1EP_4x4mm_P0.5mm_EP2.45x2.45mm,C19189323
HT7533-1,U8,SOT-89-3_L4.5-W2.5-P1.50-LS4.2-BR,C14289

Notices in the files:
README.md:
📜 License:
MeshCore is open-source software released under the MIT License. You are free to use, modify, and distribute it for personal and commercial projects.
